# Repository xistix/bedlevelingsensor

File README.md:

# bedlevelingsensor
xISTIx bed leveling sensor board

Eagle schematics and board file for the bed leveling sensor.

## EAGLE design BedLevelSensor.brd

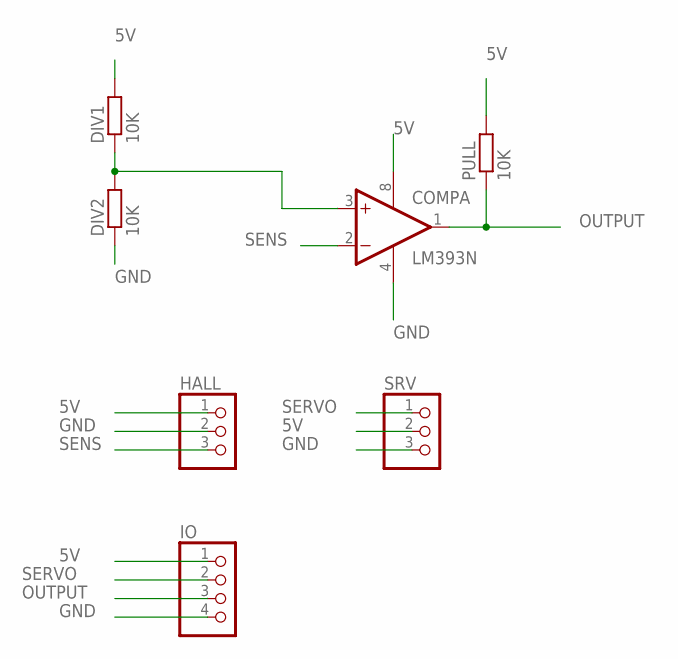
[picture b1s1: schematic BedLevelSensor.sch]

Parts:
COMP: LM393N; DIL08
DIV1, DIV2: 10K; 0204/5
HALL: PINHD-1X3; 1X03
IO: PINHD-1X4; 1X04
PULL: 10K; 0204/5
SRV: PINHD-1X3; 1X03

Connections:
5V: COMP.8 (V+), DIV1.2, HALL.1, IO.1, PULL.2, SRV.2
GND: COMP.4 (V-), DIV2.1, HALL.2, IO.4, SRV.3
unnamed: COMP.3 (+IN), DIV1.1, DIV2.2
OUTPUT: COMP.1 (OUT), IO.3, PULL.1
SENS: COMP.2 (-IN), HALL.3
SERVO: IO.2, SRV.1

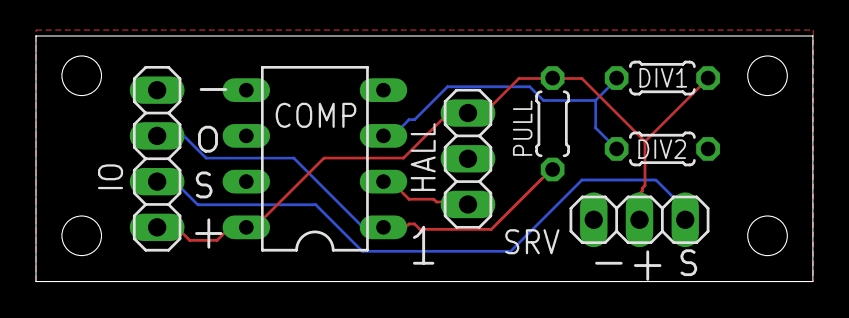
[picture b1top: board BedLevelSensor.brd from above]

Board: 2 copper layers, 43.2 x 13.6 mm, 7 parts (0 on the bottom side), 6 nets.
